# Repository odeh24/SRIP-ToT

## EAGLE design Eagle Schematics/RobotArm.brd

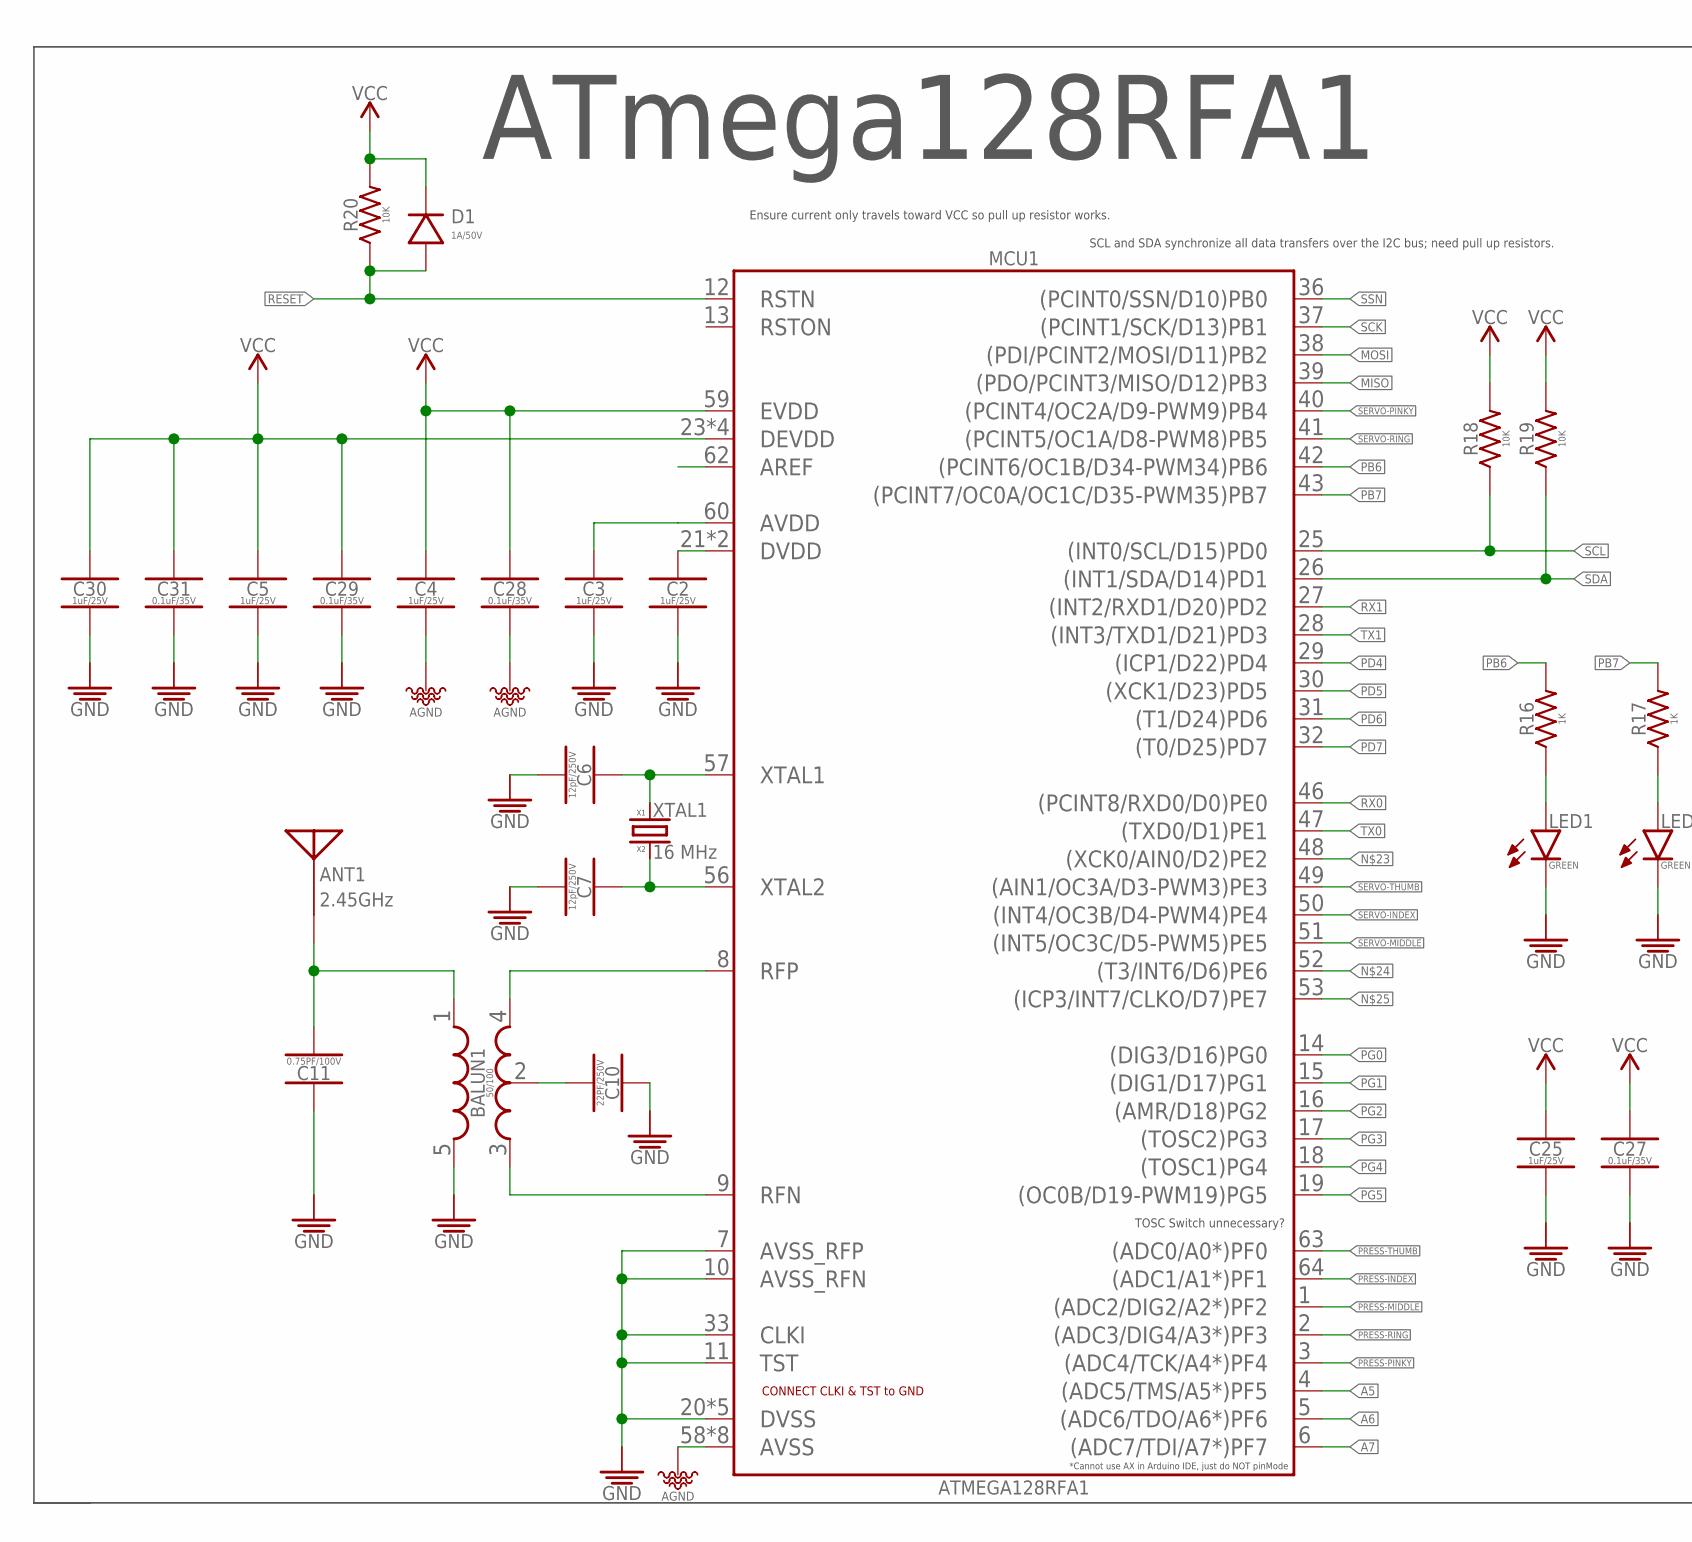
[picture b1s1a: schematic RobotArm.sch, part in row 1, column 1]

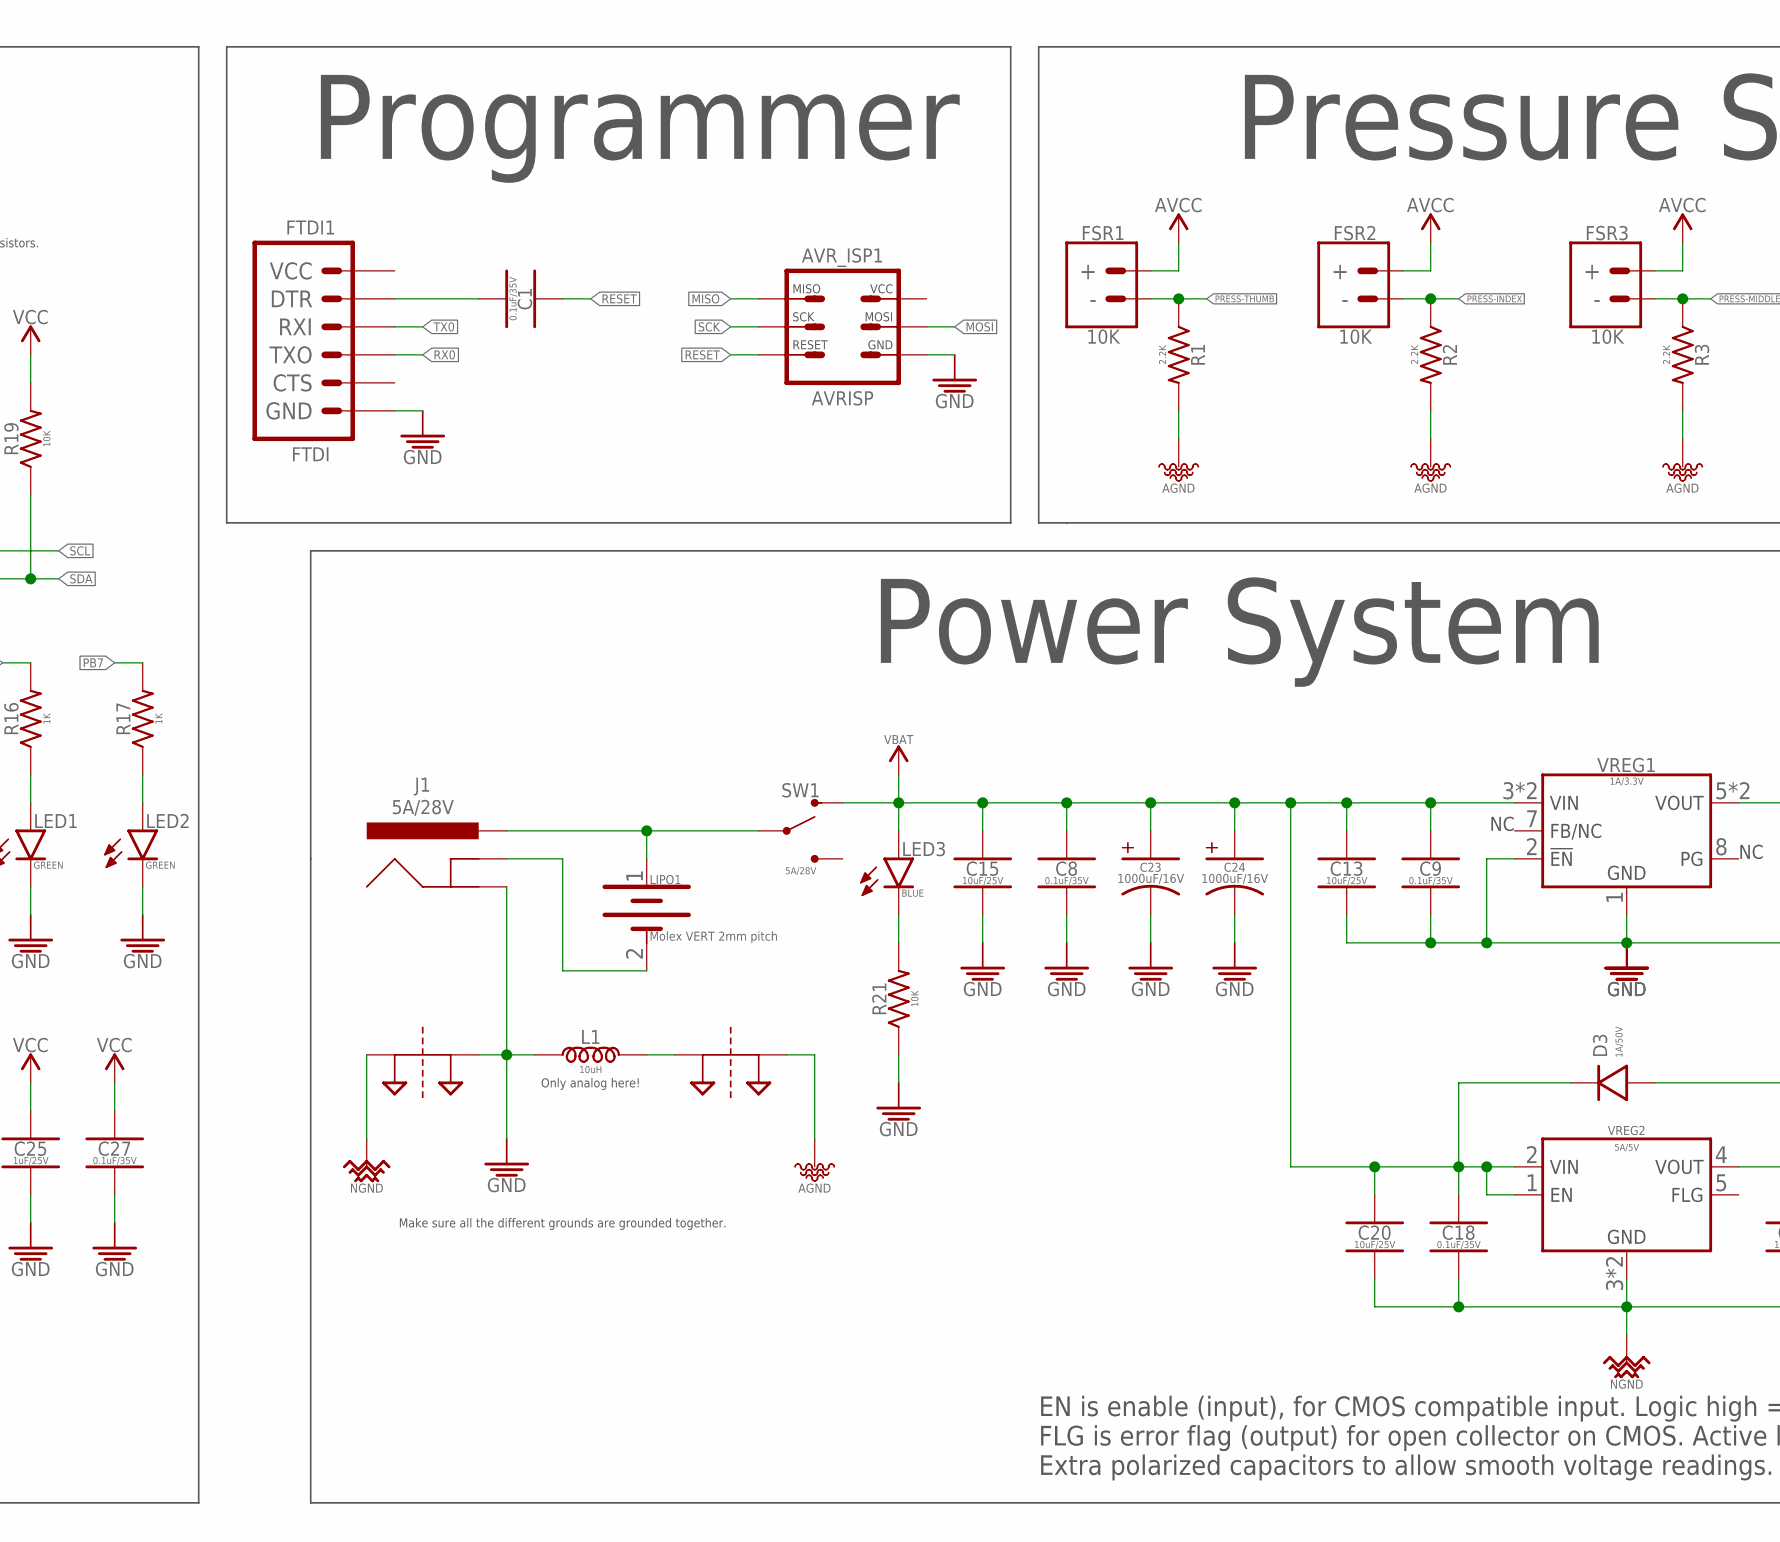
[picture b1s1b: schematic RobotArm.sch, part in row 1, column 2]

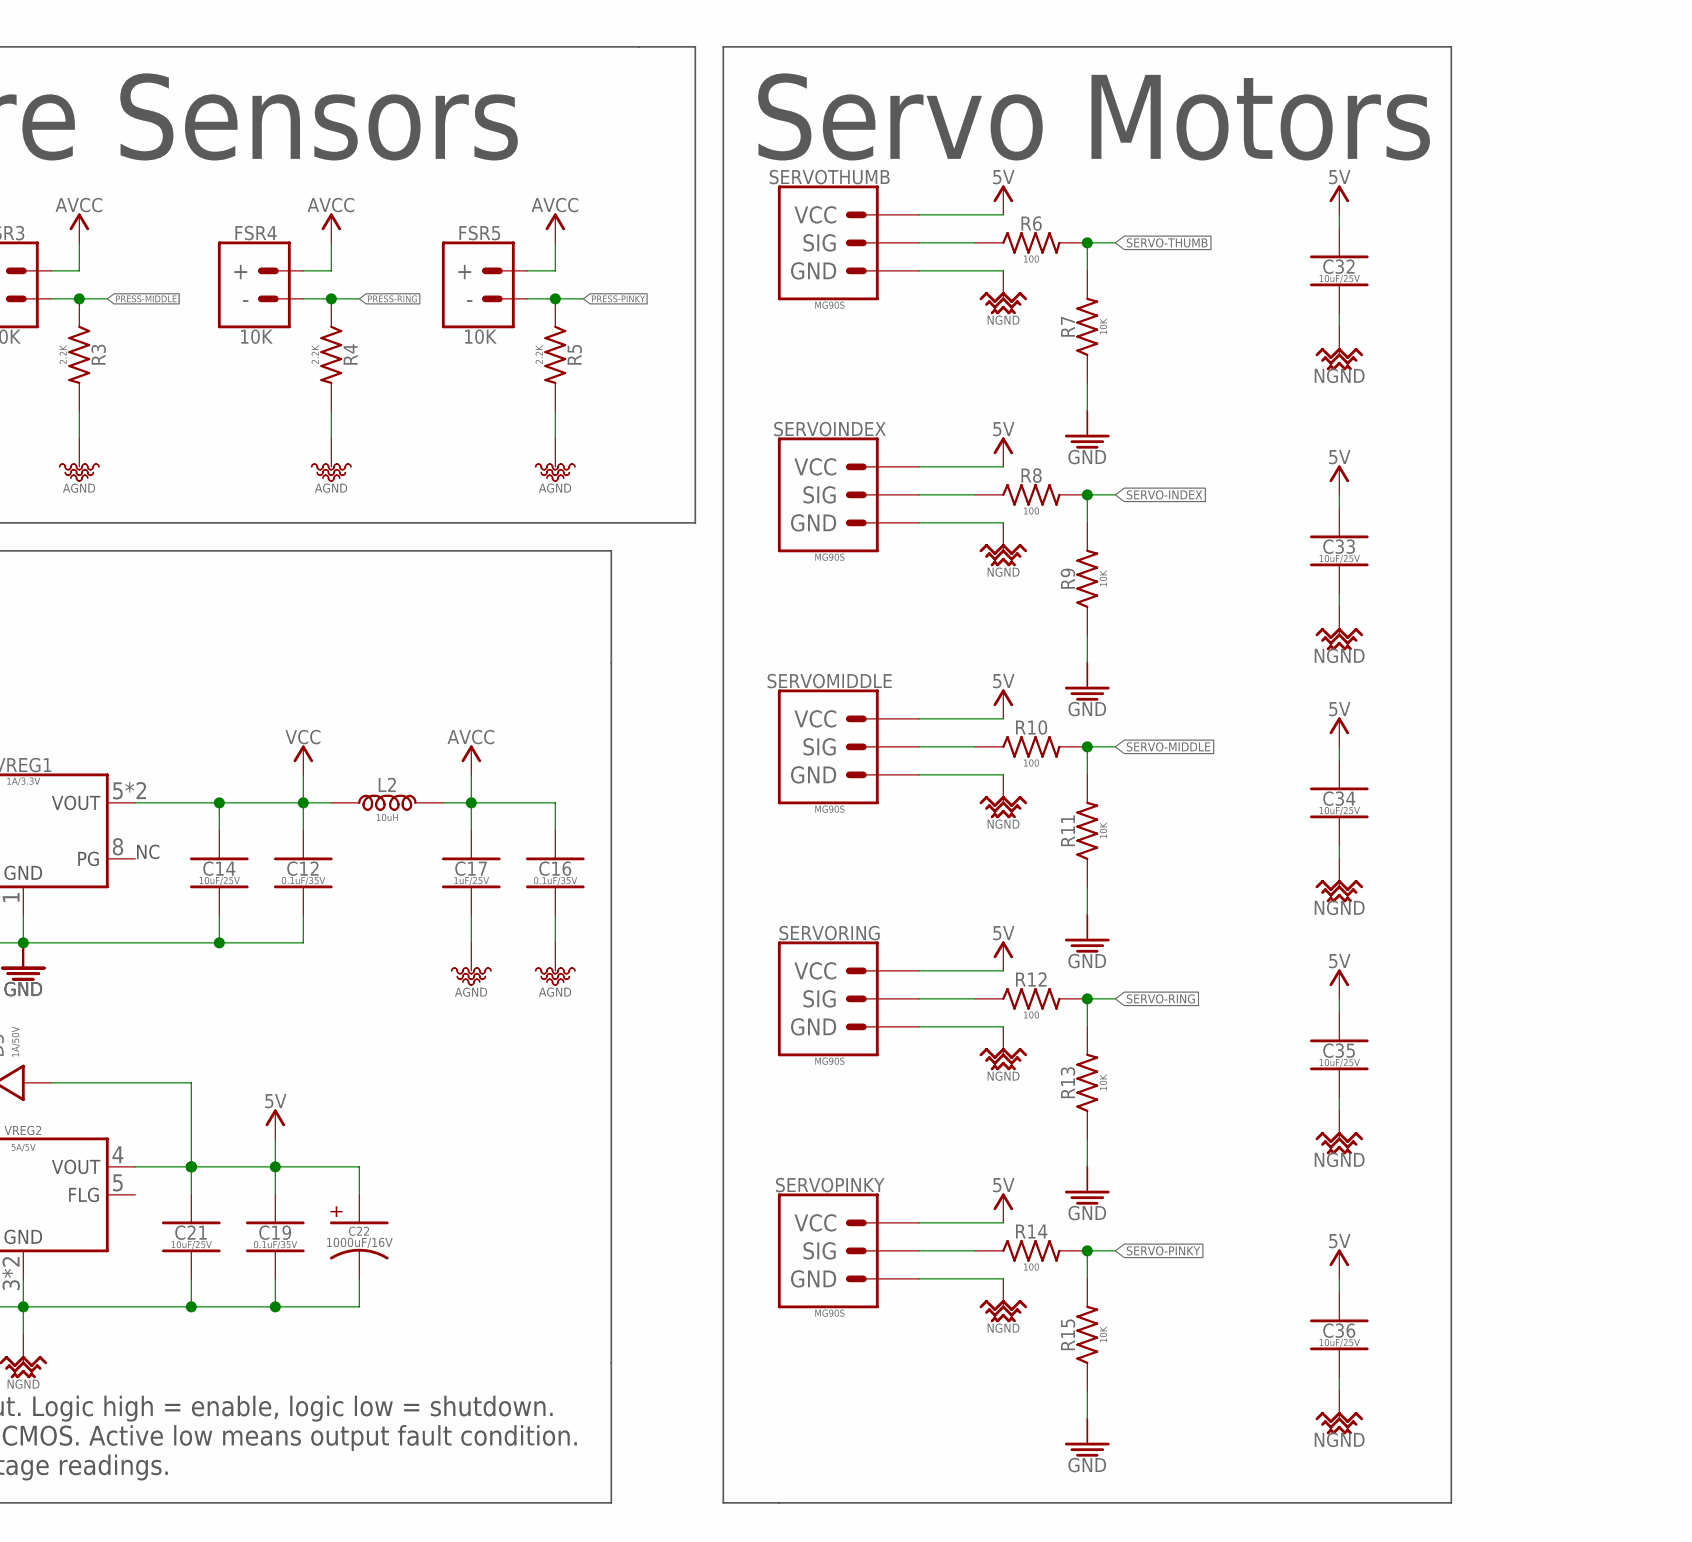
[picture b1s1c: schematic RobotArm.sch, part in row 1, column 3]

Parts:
ANT1: 2.45GHz; ANTC6522X100
AVR_ISP1: AVRISP; 2X3-NS
BALUN1: 50/100; RESCAXE65P200X125X95-6
C1, C8, C9, C12, C16, C18, C19, C27, C28, C29, C31: 0.1uF/35V; CAPC2012X95_SMD-0805
C2, C3, C4, C5, C17, C25, C30: 1uF/25V; CAPC2012X95_SMD-0805
C6, C7: 12pF/250V; CAPC2012X95_SMD-0805
C10: 22PF/250V; _CER_SMD-805
C11: 0.75PF/100V; _CER_SMD-805
C13, C14, C15, C20, C21, C32, C33, C34, C35, C36: 10uF/25V; CAPC2012X95_SMD-0805
C22, C23, C24: 1000uF/16V; _AE_PTH_DIA8-LS3.5-H21.50
D1, D3: 1A/50V; SODFL3516X170
FSR1, FSR2, FSR3, FSR4, FSR5: 10K; _MOLEX-0530470210_VERT_PITCH-1.25MM
FTDI1: FTDI; FTDI_BASIC-6PIN-MALE-RA
J1: 5A/28V; POWER_JACK_PTH_ID2.1MM-OD5.5MM
L1, L2: 10uH; _SMD-805
LED1, LED2: GREEN; LEDC2012X120_LED-0805
LED3: BLUE; LEDC2012X120_LED-0805
LIPO1: Molex VERT 2mm pitch; _MOLEX-89400_VERT_PITCH-2MM
MCU1: ATMEGA128RFA1; QFN50P900X900X90-64
NET_BRIDGE1, NET_BRIDGE2: 2PT_GND_TIE
R1, R2, R3, R4, R5: 2.2K; RESC2012X60_SMD-0805
R6, R8, R10, R12, R14: 100; RESC2012X60_SMD-0805
R7, R9, R11, R13, R15, R18, R19, R20, R21: 10K; RESC2012X60_SMD-0805
R16, R17: 1K; RESC2012X60_SMD-0805
SERVOINDEX: MG90S; 1X03-VERT-MALE
SERVOMIDDLE: MG90S; 1X03-VERT-MALE
SERVOPINKY: MG90S; 1X03-VERT-MALE
SERVORING: MG90S; 1X03-VERT-MALE
SERVOTHUMB: MG90S; 1X03-VERT-MALE
SW1: 5A/28V; SW_TOGGLE_SPDT_5A-28V_13L-7W
VREG1: 1A/3.3V; SOIC127P600X265-8
VREG2: 5A/5V; TO170P1363X457-6
XTAL1: 16 MHz; OSCCC500X320X110

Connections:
5V: C19.1, C21.1, C22.+ (A), C32.1, C33.1, C34.1, C35.1, C36.1, D3.A, SERVOINDEX.VCC, SERVOMIDDLE.VCC, SERVOPINKY.VCC, SERVORING.VCC, SERVOTHUMB.VCC, VREG2.4 (VOUT)
+: J1.PWR, LIPO1.1 (+), SW1.P
-: J1.GND@1 (GND), LIPO1.2 (-)
A5: MCU1.4 ((ADC5/TMS/A5*)PF5)
A6: MCU1.5 ((ADC6/TDO/A6*)PF6)
A7: MCU1.6 ((ADC7/TDI/A7*)PF7)
AVCC: C16.1, C17.1, L2.2
MISO: AVR_ISP1.MISO, MCU1.39 ((PDO/PCINT3/MISO/D12)PB3)
MOSI: AVR_ISP1.MOSI, MCU1.38 ((PDI/PCINT2/MOSI/D11)PB2)
unnamed: R6.1, SERVOTHUMB.SIG
unnamed: LED1.A, R16.1
unnamed: R8.1, SERVOINDEX.SIG
unnamed: R10.1, SERVOMIDDLE.SIG
unnamed: R12.1, SERVORING.SIG
unnamed: R14.1, SERVOPINKY.SIG
unnamed: LED2.A, R17.1
unnamed: C6.1, MCU1.57 (XTAL1), XTAL1.1 (XTAL1)
unnamed: C7.1, MCU1.56 (XTAL2), XTAL1.3 (XTAL2)
unnamed: C1.2, FTDI1.DTR
unnamed: BALUN1.4 (OUT2), MCU1.8 (RFP)
unnamed: BALUN1.3 (OUT1), MCU1.9 (RFN)
unnamed: C3.1, MCU1.60 (AVDD)
unnamed: C2.1, MCU1.21 (DVDD), MCU1.22 (DVDD)
unnamed: BALUN1.2 (GND), C10.2
unnamed: ANT1.1, BALUN1.1 (IN), C11.2
unnamed: L1.2, NET_BRIDGE2.P$1
unnamed: LED3.K, R21.2
NGND: C18.2, C19.2, C20.2, C21.2, C22.- (K), C32.2, C33.2, C34.2, C35.2, C36.2, NET_BRIDGE1.P$1, SERVOINDEX.GND, SERVOMIDDLE.GND, SERVOPINKY.GND, SERVORING.GND, SERVOTHUMB.GND, VREG2.3 (GND), VREG2.6 (GND)
PB6: MCU1.42 ((PCINT6/OC1B/D34-PWM34)PB6), R16.2
PB7: MCU1.43 ((PCINT7/OC0A/OC1C/D35-PWM35)PB7), R17.2
PD4: MCU1.29 ((ICP1/D22)PD4)
PD5: MCU1.30 ((XCK1/D23)PD5)
PD6: MCU1.31 ((T1/D24)PD6)
PD7: MCU1.32 ((T0/D25)PD7)
PG0: MCU1.14 ((DIG3/D16)PG0)
PG1: MCU1.15 ((DIG1/D17)PG1)
PG2: MCU1.16 ((AMR/D18)PG2)
PG3: MCU1.17 ((TOSC2)PG3)
PG4: MCU1.18 ((TOSC1)PG4)
PG5: MCU1.19 ((OC0B/D19-PWM19)PG5)
PRESS-INDEX: FSR2.2 (-), MCU1.64 ((ADC1/A1*)PF1), R2.1
PRESS-MIDDLE: FSR3.2 (-), MCU1.1 ((ADC2/DIG2/A2*)PF2), R3.1
PRESS-PINKY: FSR5.2 (-), MCU1.3 ((ADC4/TCK/A4*)PF4), R5.1
PRESS-RING: FSR4.2 (-), MCU1.2 ((ADC3/DIG4/A3*)PF3), R4.1
PRESS-THUMB: FSR1.2 (-), MCU1.63 ((ADC0/A0*)PF0), R1.1
RESET: AVR_ISP1.RESET, C1.1, D1.A, MCU1.12 (RSTN), R20.1
RX0: FTDI1.TXO, MCU1.46 ((PCINT8/RXD0/D0)PE0)
RX1: MCU1.27 ((INT2/RXD1/D20)PD2)
SCK: AVR_ISP1.SCK, MCU1.37 ((PCINT1/SCK/D13)PB1)
SCL: MCU1.25 ((INT0/SCL/D15)PD0), R18.1
SDA: MCU1.26 ((INT1/SDA/D14)PD1), R19.1
SERVO-INDEX: MCU1.50 ((INT4/OC3B/D4-PWM4)PE4), R8.2, R9.2
SERVO-MIDDLE: MCU1.51 ((INT5/OC3C/D5-PWM5)PE5), R10.2, R11.2
SERVO-PINKY: MCU1.40 ((PCINT4/OC2A/D9-PWM9)PB4), R14.2, R15.2
SERVO-RING: MCU1.41 ((PCINT5/OC1A/D8-PWM8)PB5), R12.2, R13.2
SERVO-THUMB: MCU1.49 ((AIN1/OC3A/D3-PWM3)PE3), R6.2, R7.2
SSN: MCU1.36 ((PCINT0/SSN/D10)PB0)
TX0: FTDI1.RXI, MCU1.47 ((TXD0/D1)PE1)
TX1: MCU1.28 ((INT3/TXD1/D21)PD3)
VBAT: C8.1, C9.1, C13.1, C15.1, C18.1, C20.1, C23.+ (A), C24.+ (A), D3.K, LED3.A, SW1.S1, VREG1.3 (VIN), VREG1.4 (VIN), VREG2.1 (EN), VREG2.2 (VIN)
VCC: C4.1, C5.1, C12.1, C14.1, C25.1, C27.1, C28.1, C29.1, C30.1, C31.1, D1.K, FSR1.1 (+), FSR2.1 (+), FSR3.1 (+), FSR4.1 (+), FSR5.1 (+), L2.1, MCU1.23 (DEVDD), MCU1.34 (DEVDD), MCU1.44 (DEVDD), MCU1.54 (DEVDD), MCU1.59 (EVDD), R18.2, R19.2, R20.2, VREG1.5 (VOUT), VREG1.6 (VOUT)

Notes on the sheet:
ATmega128RFA1
Pressure Sensors
Power System
Programmer
Servo Motors
SCL and SDA synchronize all data transfers over the I2C bus; need pull up resistors.
TOSC Switch unnecessary?
Ensure current only travels toward VCC so pull up resistor works.
Make sure all the different grounds are grounded together.
Only analog here!
EN is enable (input), for CMOS compatible input. Logic high = enable, logic low = shutdown. FLG is error flag (output) for open collector on CMOS. Active low means output fault condition. Extra polarized capacitors to allow smooth voltage readings.

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
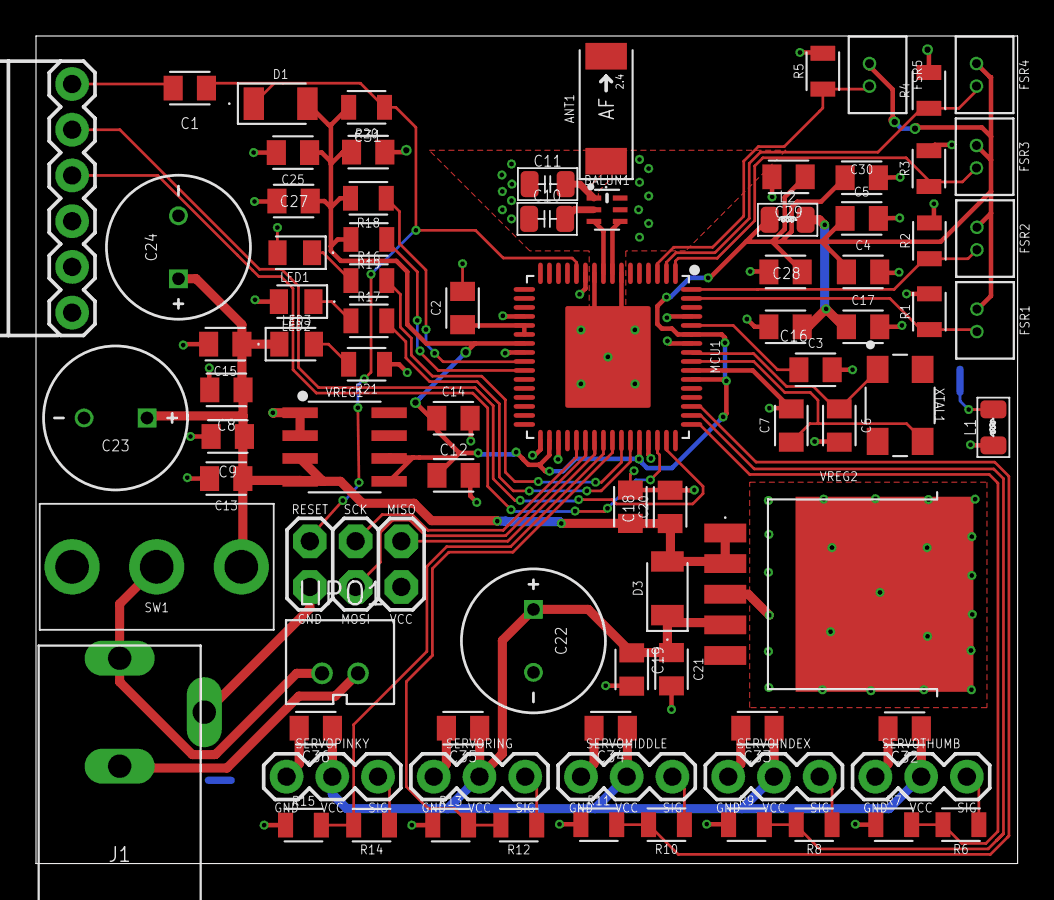
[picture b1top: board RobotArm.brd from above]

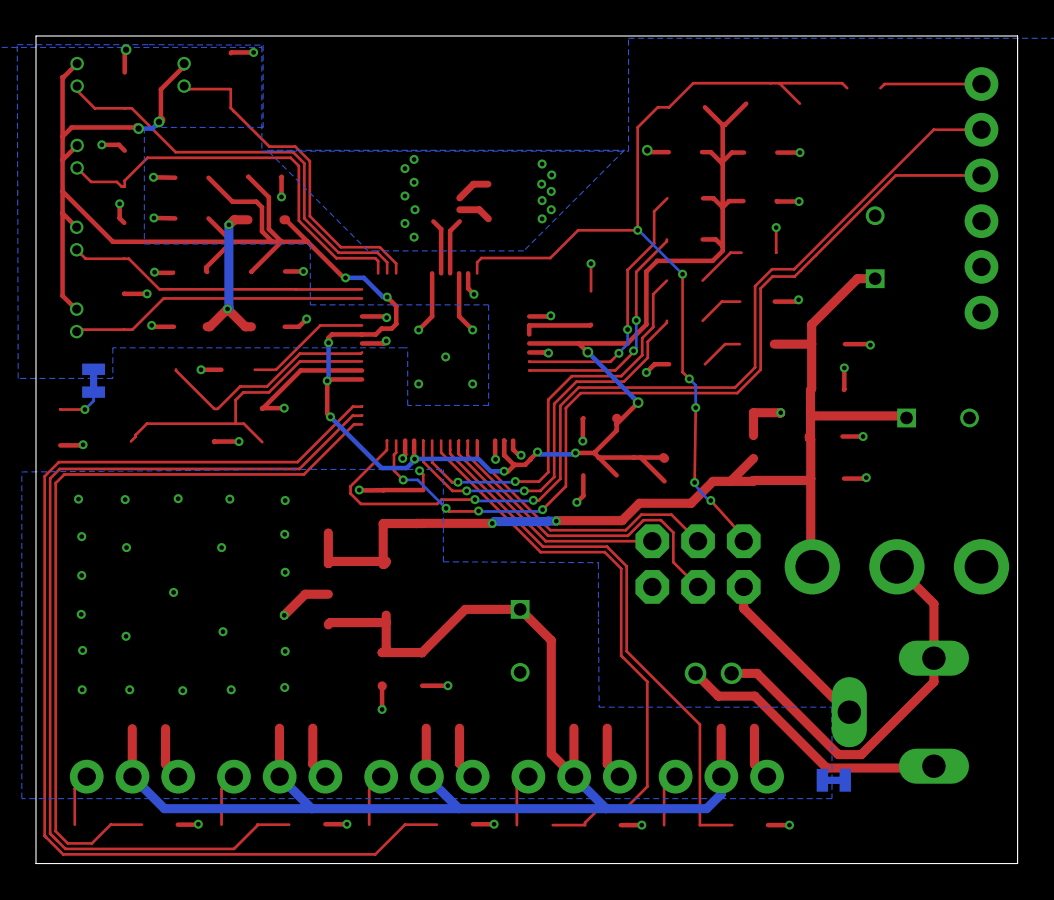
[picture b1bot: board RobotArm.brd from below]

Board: 2 copper layers, 54.5 x 46.0 mm, 86 parts (2 on the bottom side), 47 nets.
